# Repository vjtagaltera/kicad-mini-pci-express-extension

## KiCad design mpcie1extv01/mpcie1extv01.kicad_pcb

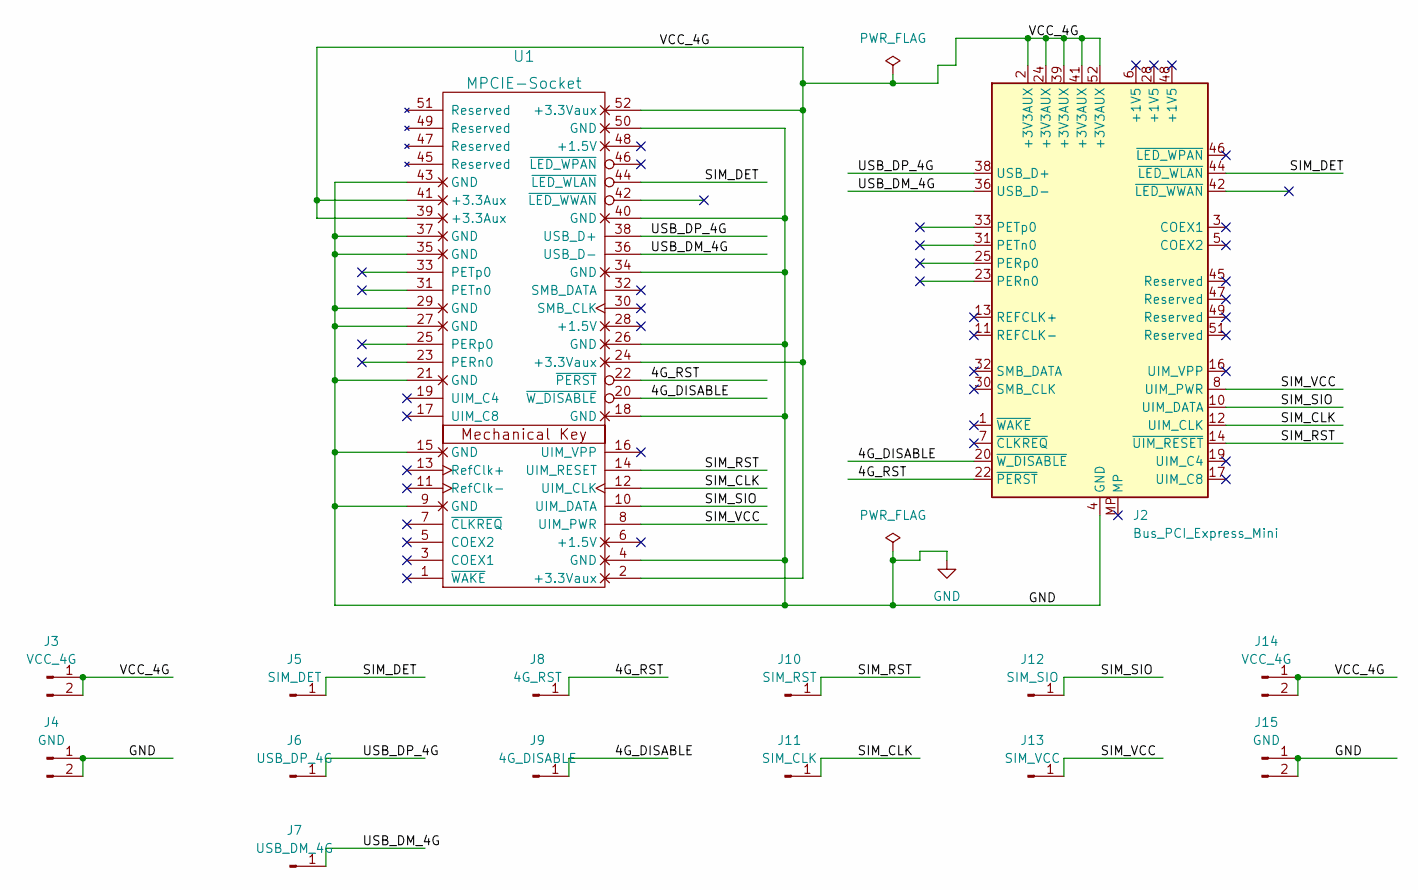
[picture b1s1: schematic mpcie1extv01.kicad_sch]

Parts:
J2: Bus_PCI_Express_Mini; BUS_PCI_Express_Mini_Dual
J3, J14: VCC_4G; PinHeader_1x02_P2.54mm_Vertical
J4, J15: GND; PinHeader_1x02_P2.54mm_Vertical
J5: SIM_DET; PinHeader_1x01_P2.54mm_Vertical
J6: USB_DP_4G; PinHeader_1x01_P2.54mm_Vertical
J7: USB_DM_4G; PinHeader_1x01_P2.54mm_Vertical
J8: 4G_RST; PinHeader_1x01_P2.54mm_Vertical
J9: 4G_DISABLE; PinHeader_1x01_P2.54mm_Vertical
J10: SIM_RST; PinHeader_1x01_P2.54mm_Vertical
J11: SIM_CLK; PinHeader_1x01_P2.54mm_Vertical
J12: SIM_SIO; PinHeader_1x01_P2.54mm_Vertical
J13: SIM_VCC; PinHeader_1x01_P2.54mm_Vertical
U1: MPCIE-Socket; mpcie-full-card

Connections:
/4G_DISABLE: J2.20 (~W_DISABLE), J9.1, U1.20 (~W_DISABLE)
/4G_RST: J2.22 (~PERST), J8.1, U1.22 (~PERST)
/SIM_CLK: J2.12 (UIM_CLK), J11.1, U1.12 (UIM_CLK)
/SIM_DET: J2.44 (~LED_WLAN), J5.1, U1.44 (~LED_WLAN)
/SIM_RST: J2.14 (~UIM_RESET), J10.1, U1.14 (UIM_RESET)
/SIM_SIO: J2.10 (UIM_DATA), J12.1, U1.10 (UIM_DATA)
/SIM_VCC: J2.8 (UIM_PWR), J13.1, U1.8 (UIM_PWR)
/USB_DM_4G: J2.36 (USB_D-), J7.1, U1.36 (USB_D-)
/USB_DP_4G: J2.38 (USB_D+), J6.1, U1.38 (USB_D+)
/VCC_4G: J2.2 (+3V3AUX), J2.24 (+3V3AUX), J2.39 (+3V3AUX), J2.41 (+3V3AUX), J2.52 (+3V3AUX), J3.1, J3.2, J14.1, J14.2, U1.2 (+3.3Vaux), U1.24 (+3.3Vaux), U1.39 (+3.3Aux), U1.41 (+3.3Aux), U1.52 (+3.3Vaux)
GND: J2.4 (GND), J2.9 (GND), J2.15 (GND), J2.18 (GND), J2.21 (GND), J2.26 (GND), J2.27 (GND), J2.29 (GND), J2.34 (GND), J2.35 (GND), J2.37 (GND), J2.40 (GND), J2.43 (GND), J2.50 (GND), J4.1, J4.2, J15.1, J15.2, U1.4 (GND), U1.9 (GND), U1.15 (GND), U1.18 (GND), U1.21 (GND), U1.26 (GND), U1.27 (GND), U1.29 (GND), U1.34 (GND), U1.35 (GND), U1.37 (GND), U1.40 (GND), U1.43 (GND), U1.50 (GND)

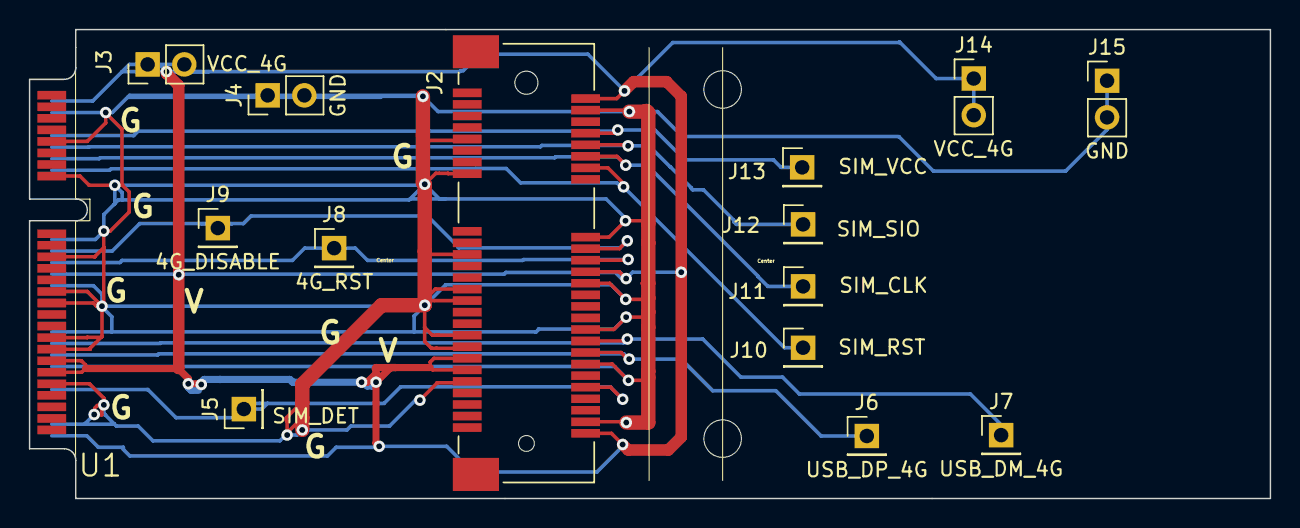
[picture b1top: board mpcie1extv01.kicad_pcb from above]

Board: 2 copper layers, 86.0 x 32.5 mm, 15 parts (0 on the bottom side), 11 nets.

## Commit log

2022-07-29 initial mpcie extension board design and output files
2022-07-29 remove unnecessary _Paste files
2022-07-29 reference documents
2022-07-29 copy license file header of github.com/pcbt/kicad-mini-pci-express/ to its directory
2022-07-29 copy github.com/pcbt/kicad-mini-pci-express/ symbol files and footprint files locally
